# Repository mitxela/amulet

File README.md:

# UV Protection Amulet

Source code and KiCad design files for the [UV Protection Amulet](https://mitxela.com/projects/amulet).

Uses an ATtiny84, a TTP223 Capacitive sensing chip and the VEML6075 UV sensor. The PCB thickness is 0.8mm and the battery is a CR2032 3V Lithium coin cell.

The i2c routines were modified to not require external pullup resistors. 

License: GPL v3

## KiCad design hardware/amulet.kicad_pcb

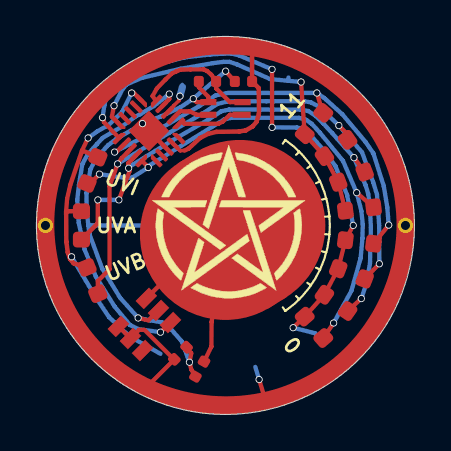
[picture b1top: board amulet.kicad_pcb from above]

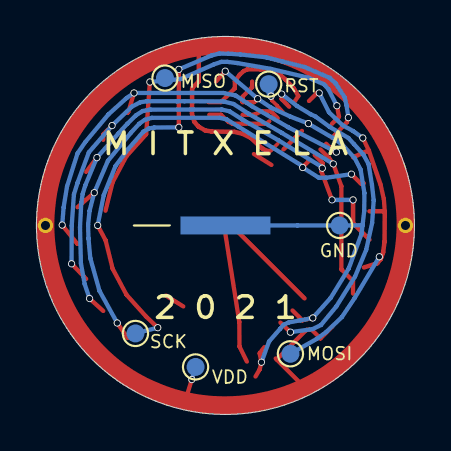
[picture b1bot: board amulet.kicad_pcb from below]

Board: 2 copper layers, 21.0 x 21.0 mm, 29 parts (7 on the bottom side), 15 nets.

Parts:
C1, C2, C3: 100n; C_0402_1005Metric
C4: 30pF; C_0402_1005Metric
D1, D2, D3, D4, D5, D6, D7, D8, D9, D10, D11: LED; LED_0603_1608Metric
TP1: Case; amulet
TP2: Tab; TestPoint_Pad_D1.0mm
TP3, TP3#2: CapSense; TestPoint_Pad_D1.0mm
TP4: RST; TestPoint_Pad_D1.0mm
TP5: GND; TestPoint_Pad_D1.0mm
TP6: VDD; TestPoint_Pad_D1.0mm
TP7: SCK; TestPoint_Pad_D1.0mm
TP8: MISO; TestPoint_Pad_D1.0mm
TP9: MOSI; TestPoint_Pad_D1.0mm
U1: ATtiny84A-MMH; QFN-20-1EP_3x3mm_P0.45mm_EP1.6x1.6mm
U2: TTP223-BA6; SOT-23-6
U3: VEML6075
pentagram: G***; pentagram

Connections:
/BUTTON: U1.14, U2.1
/CapSense: C4.2, TP3.1, TP3#2.1, U2.3
/PA4: D1.1, D2.1, D3.1, D4.1, TP7.1, U1.1
/PA5: D5.1, D6.1, D7.1, D8.1, TP8.1, U1.20
/PA6: D9.1, D10.1, D11.1, TP9.1, U1.16
/SCL: U1.11, U3.3
/SDA: U1.12, U3.2
/VEML6075_Power: C2.2, U1.15, U3.4
GND: C1.1, C2.1, C3.1, C4.1, TP2.1, TP5.1, U1.8, U1.21, U2.2, U3.1
unnamed: D1.2, D5.2, D9.2, U1.5
unnamed: D4.2, D8.2, U1.2
unnamed: D2.2, D6.2, D10.2, U1.4
unnamed: D3.2, D7.2, D11.2, U1.3
unnamed: TP4.1, U1.13
VDD: C1.2, C3.2, TP1.1, TP6.1, U1.9, U2.4, U2.5

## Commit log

2021-06-08 bar graph
2021-06-08 Display UVI
2021-06-08 buspirate python script
2021-06-09 Modes
2021-06-09 Add startup animation
2021-06-09 Increase resolution, reduce power consumption
2021-06-09 Poweroff timeout, reinit on wakeup
2021-06-09 Use PA7 to power sensor
2021-06-09 Port to ATtiny84
2021-06-10 Use internal pullups for i2c
2021-06-11 Initial layout
2021-06-11 Add programming test points
2021-06-11 Add UV star and graph markers
2021-06-12 Final fixes
2021-06-12 gerber settings
2021-07-07 Final adjustments to behaviour
2021-10-25 Change symbol to pentagram
2021-10-25 Add SVG files to repo
2021-10-25 Add gerber files
2021-10-29 Add README
